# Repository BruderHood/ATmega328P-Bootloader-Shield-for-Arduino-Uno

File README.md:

# ATmega328P-Bootloader-Shield-for-Arduino-Uno
This project showcases a custom-designed PCB that acts as an attachment board (shield) for the Arduino Uno. The board simplifies the process of bootloading ATmega328P microcontrollers by providing an easy-to-use interface.

Features:

Custom PCB Design: A unique shield designed specifically for the ATmega328P, featuring pinouts clearly labeled to facilitate easy connection with the Arduino Uno.
Arduino Uno Compatible: Simply plug this shield into an Arduino Uno and use it to burn bootloaders onto ATmega328P chips.
Minimal Components: The board uses only the necessary components such as resistors, capacitors, and crystals to ensure proper bootloading functionality.
Pinout Labels: All relevant ATmega328P pins (P0–P28) are clearly labeled, along with their corresponding Arduino Uno pins for ease of use.
Oscillator and Reset Circuit: Includes a crystal oscillator and a manual reset switch for reliable clock signal generation and reset control.

How It Works:

This shield is designed to simplify the process of bootloading ATmega328P microcontrollers using the Arduino Uno as an In-System Programmer (ISP). Simply insert an ATmega328P into the ZIF (Zero Insertion Force) socket, connect the Arduino Uno, and follow the typical bootloading process via the Arduino IDE.

Insert the ATmega328P: Place the microcontroller into the ZIF socket.
Plug the Shield into Arduino Uno: This shield is designed to fit directly onto the Arduino Uno.
Open Arduino IDE: Select the appropriate board and burn the bootloader via the “Burn Bootloader” option.

Components:

ZIF Socket: Allows easy insertion and removal of ATmega328P chips without the need for soldering.
16 MHz Crystal Oscillator: Ensures a stable clock signal required by the ATmega328P.
Capacitors: Decoupling capacitors to ensure smooth operation.
Reset Button: Provides manual reset control.

Usage:

Insert the ATmega328P microcontroller into the ZIF socket.
Connect the board to the Arduino Uno.
Open Arduino IDE and select Tools > Board > Arduino Uno.
Go to Tools > Programmer > Arduino as ISP.
Click Tools > Burn Bootloader to load the bootloader onto the ATmega328P.

License

This project is open-source and can be freely used and modified. Contributions and improvements are welcome!

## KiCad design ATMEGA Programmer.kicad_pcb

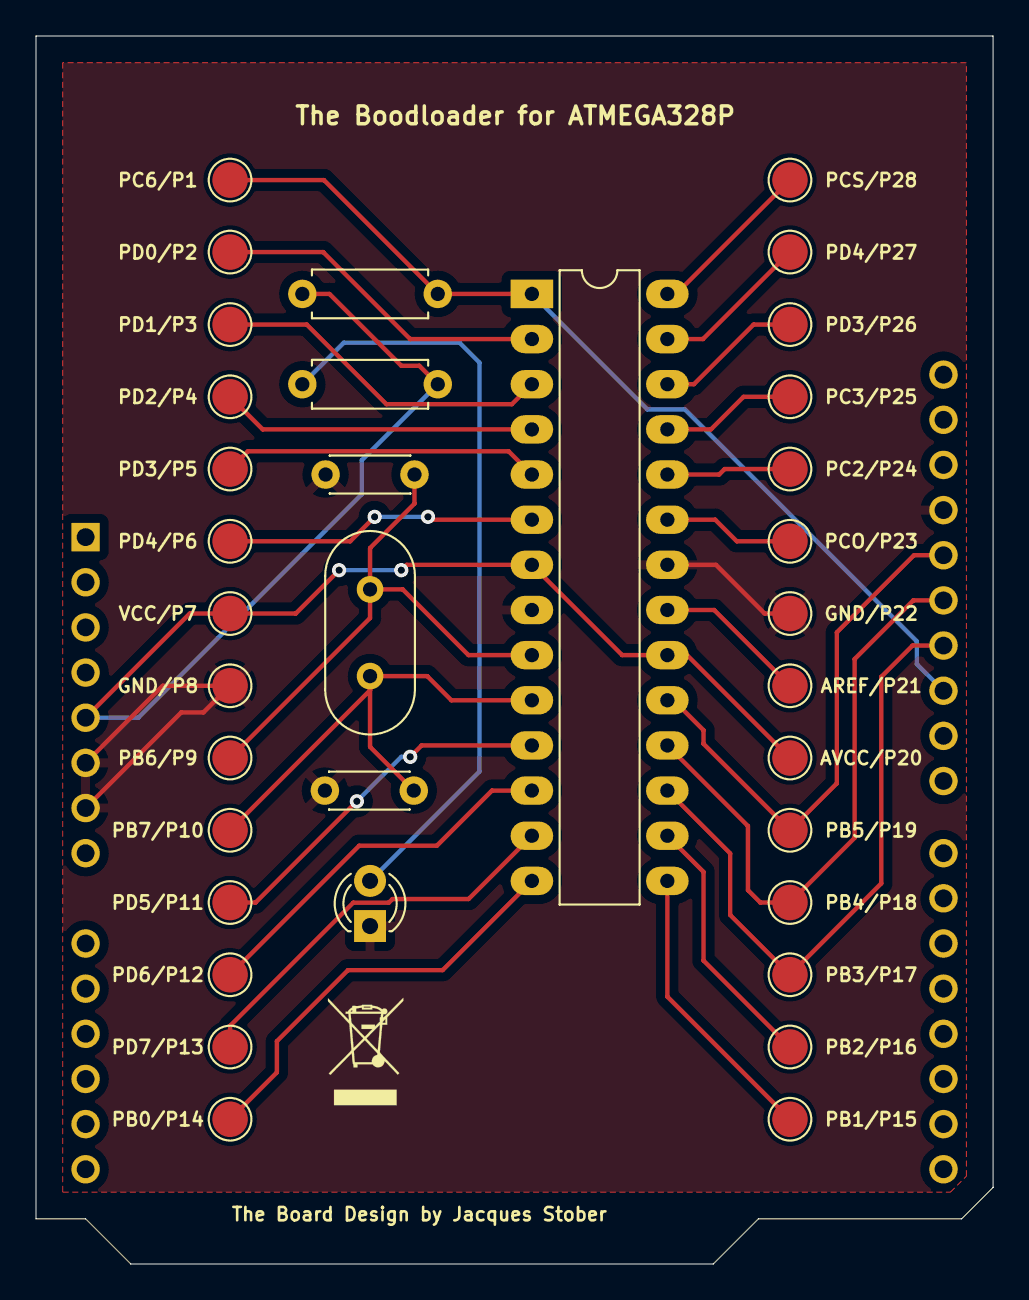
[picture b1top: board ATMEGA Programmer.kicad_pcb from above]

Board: 2 copper layers, 53.8 x 69.1 mm, 36 parts (1 on the bottom side), 27 nets.

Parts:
A1: Arduino_UNO_R3
AREF/P21: TestPoint; TestPoint_Pad_D2.0mm
AVCC/P20: TestPoint; TestPoint_Pad_D2.0mm
C1, C2: 22pF; C_Disc_D4.3mm_W1.9mm_P5.00mm
D1: LED; LED_D3.0mm
GND/P8, GND/P22: TestPoint; TestPoint_Pad_D2.0mm
J1: Conn_01x28; DIP-28_W7.62mm_LongPads
PB0/P14, PB1/P15, PB2/P16, PB3/P17, PB4/P18, PB5/P19, PB6/P9, PB7/P10: TestPoint; TestPoint_Pad_D2.0mm
PC2/P24, PC3/P25, PC6/P1: TestPoint; TestPoint_Pad_D2.0mm
PCO/P23: TestPoint; TestPoint_Pad_D2.0mm
PCS/P28: TestPoint; TestPoint_Pad_D2.0mm
PD0/P2, PD1/P3, PD2/P4, PD3/P5, PD3/P26, PD4/P6, PD4/P27, PD5/P11, PD6/P12, PD7/P13: TestPoint; TestPoint_Pad_D2.0mm
R1: 1K; R_Axial_DIN0207_L6.3mm_D2.5mm_P7.62mm_Horizontal
R2: 10K; R_Axial_DIN0207_L6.3mm_D2.5mm_P7.62mm_Horizontal
VCC/P7: TestPoint; TestPoint_Pad_D2.0mm
Y1: Crystal; Crystal_HC49-4H_Vertical

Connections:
+5V: A1.5 (+5V), AVCC/P20.1, J1.7, J1.20, R1.1, R2.1, VCC/P7.1
D10: A1.25 (D10), J1.1, PC6/P1.1, R2.2
D11: A1.26 (D11), J1.17, PB3/P17.1
D12: A1.27 (D12), J1.18, PB4/P18.1
D13: A1.28 (D13), J1.19, PB5/P19.1
GND: A1.6 (GND), A1.7 (GND), A1.29 (GND), C1.1, C2.1, D1.1 (K), GND/P8.1, GND/P22.1, J1.8, J1.22
unnamed: D1.2 (A), R1.2
unnamed: J1.2, PD0/P2.1
unnamed: J1.3, PD1/P3.1
unnamed: J1.4, PD2/P4.1
unnamed: J1.5, PD3/P5.1
unnamed: J1.6, PD4/P6.1
unnamed: C1.2, J1.9, PB6/P9.1, Y1.2
unnamed: C2.2, J1.10, PB7/P10.1, Y1.1
unnamed: J1.11, PD5/P11.1
unnamed: J1.12, PD6/P12.1
unnamed: J1.13, PD7/P13.1
unnamed: J1.14, PB0/P14.1
unnamed: J1.15, PB1/P15.1
unnamed: J1.16, PB2/P16.1
unnamed: AREF/P21.1, J1.21
unnamed: J1.23, PCO/P23.1
unnamed: J1.24, PC2/P24.1
unnamed: J1.25, PC3/P25.1
unnamed: J1.26, PD3/P26.1
unnamed: J1.27, PD4/P27.1
unnamed: J1.28, PCS/P28.1
